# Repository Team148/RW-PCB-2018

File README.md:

# RW-PCB-2018

These PCBs are Robowrangler versions of the Talon SRX Breakout Board and a simple CAN Bus Daisy Chain Board. This is standardized around the Molex SL latching type of connector (50-57-9405 + 16-02-0087). This type of connector also connects to US Digital S5 Encoders with the same pinout pattern.

```
Talon SRX Breakout Board BOM
  Harwin M50-3000745     Qty 1 (Cut off outer 4 pins)
  Molex 15-91-3053       Qty 1
  Lite-On LTST-C150KGKT  Qty 1 (Optional)
  Susumu RG3216P-2201-D-T5   Qty 1 (Optional)
  
Based on MVRT / FRC Team 115's Open Source Design.
```

CAN Devices need to be wired into a Molex SL type connectors(50-579404 + 16-02-0087) with the H (green) paired in the middle 2 positions,
and the L's on the outer two positions. The twisted pairs need to be next to each other. Devices must be plugged
in Sequentially and the last device must be terminated with an 120 Ohm resistor (can be PDP). These boards can also
be daisy chained if above 18 devices, simply attach port 15 to another board's port 0.The port numbers are just for reference,
they do not have to correspond to CAN ID.
```
RW CAN
  Molex 70555-0038       Qty 18
```

GERBER Files are exported for SEEEDSTUDIO's FUSION Service

Optional: We recommend using the Belden 8723 060100 wire for encoders and for extending a CAN bus to/from since it both twisted pairs are individually shielded.

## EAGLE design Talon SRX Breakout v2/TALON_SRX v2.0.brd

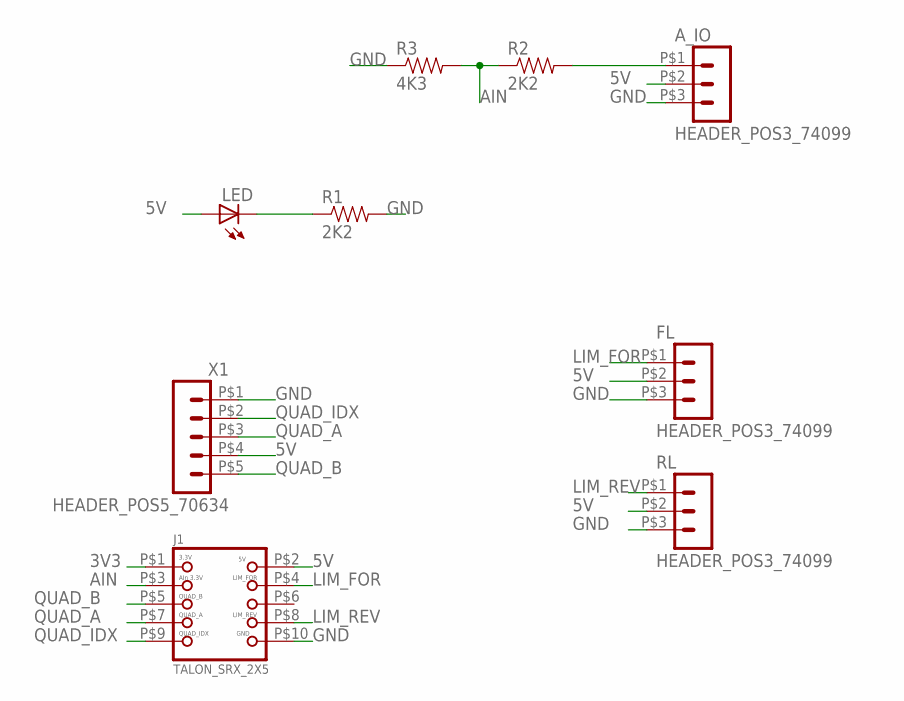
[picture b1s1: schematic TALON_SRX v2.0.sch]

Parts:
A_IO: HEADER_POS3_74099; 74099-POS3
FL: HEADER_POS3_74099; 74099-POS3
J1: TALON_SRX_2X5; 2X5-0.05-HEADER
LED: LEDSMT1206; 1206
R1, R2: 2K2; 1206
R3: 4K3; 1206
RL: HEADER_POS3_74099; 74099-POS3
X1: HEADER_POS5_70634; 70634-POS5

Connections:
3V3: J1.P$1 (1)
5V: A_IO.P$2 (2), FL.P$2 (2), J1.P$2 (2), LED.A, RL.P$2 (2), X1.P$4 (4)
AIN: J1.P$3 (3), R2.1, R3.2
GND: A_IO.P$3 (3), FL.P$3 (3), J1.P$10 (10), R1.2, R3.1, RL.P$3 (3), X1.P$1 (1)
LIM_FOR: FL.P$1 (1), J1.P$4 (4)
LIM_REV: J1.P$8 (8), RL.P$1 (1)
unnamed: A_IO.P$1 (1), R2.2
unnamed: LED.C, R1.1
QUAD_A: J1.P$7 (7), X1.P$3 (3)
QUAD_B: J1.P$5 (5), X1.P$5 (5)
QUAD_IDX: J1.P$9 (9), X1.P$2 (2)

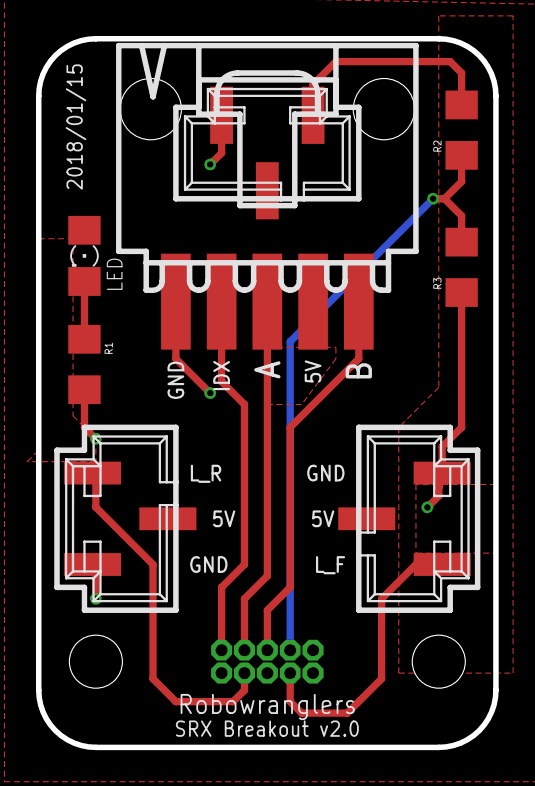
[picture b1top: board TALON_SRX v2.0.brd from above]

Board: 2 copper layers, 25.4 x 39.4 mm, 9 parts (1 on the bottom side), 10 nets.

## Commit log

2018-01-15 WIP
    Added Analog Input and Changed SMD size to 1206
2018-01-17 Made Changes
2018-01-18 Submitted to SeeedFusion
    Production Version

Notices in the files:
parts and their libraries:
SparkFun-Passives: Licensing: Creative Commons ShareAlike 4.0 International - https://creativecommons.org/licenses/by-sa/4.0
